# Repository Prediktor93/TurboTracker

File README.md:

# TurboTracker
Line follower robot

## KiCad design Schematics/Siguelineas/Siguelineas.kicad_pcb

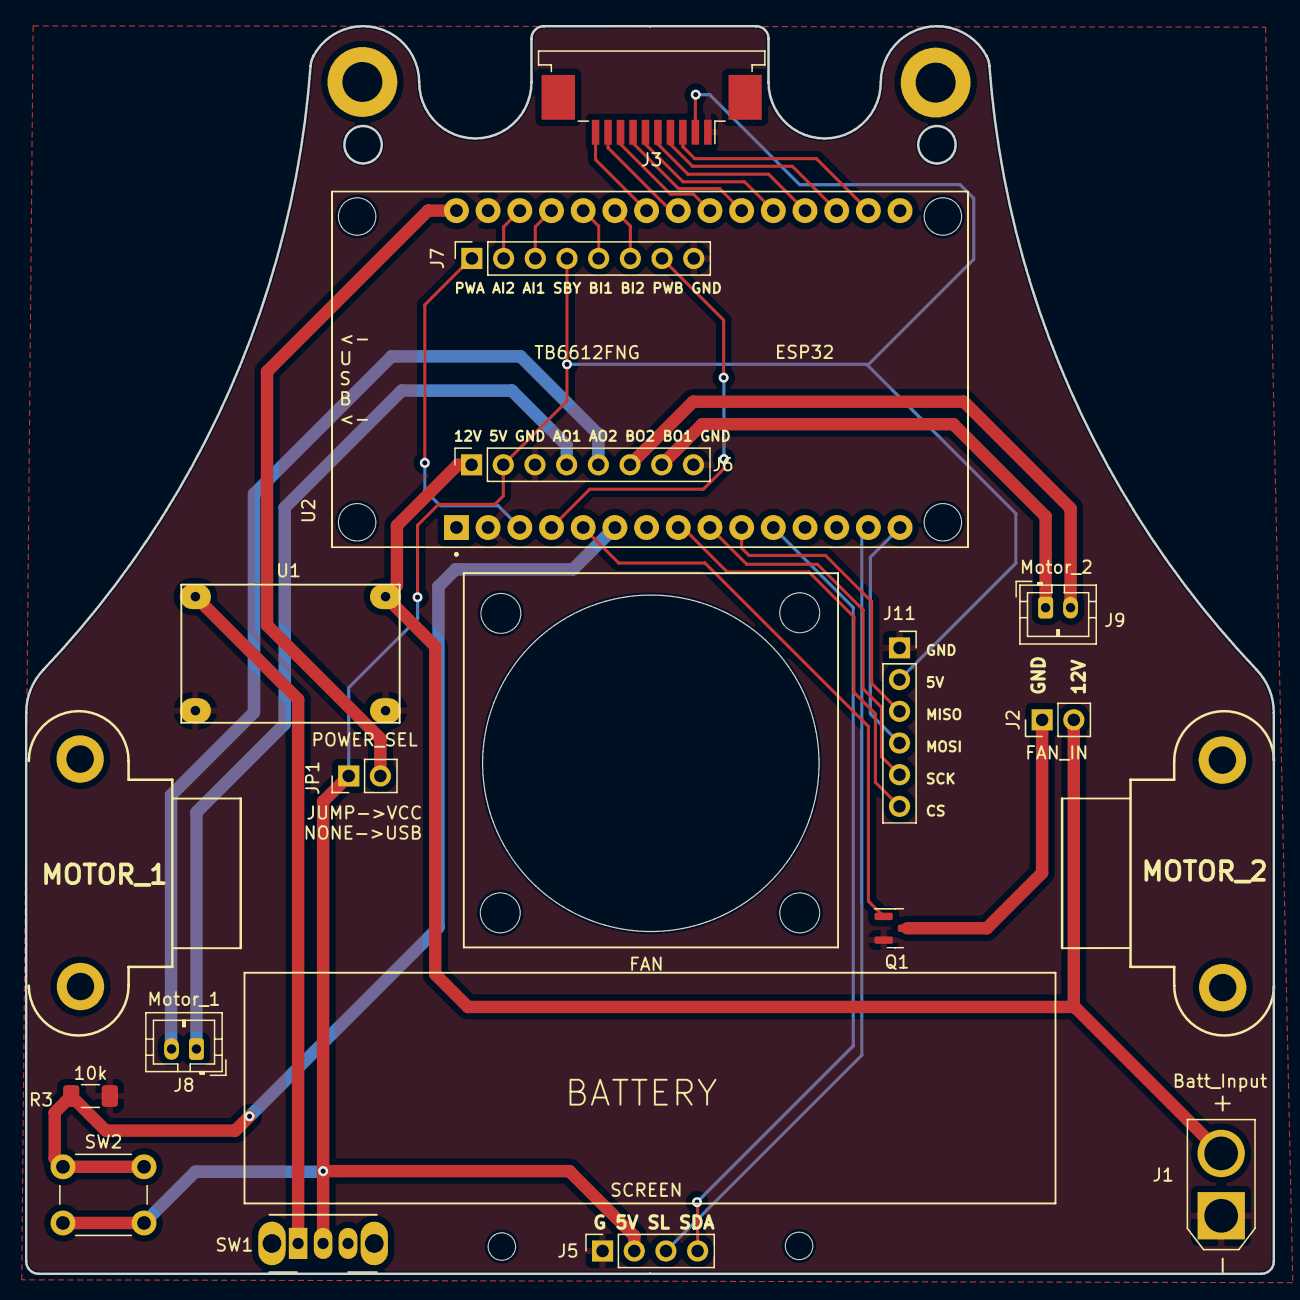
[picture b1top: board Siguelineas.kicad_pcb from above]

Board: 2 copper layers, 100.0 x 100.0 mm, 16 parts (0 on the bottom side), 32 nets.

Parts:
J1: Batt_Input; AMASS_XT30U-M_1x02_P5.0mm_Vertical
J2: FAN_IN; PinHeader_1x02_P2.54mm_Vertical
J3: Line_Sensors; TE_1-84952-0_1x10-1MP_P1.0mm_Horizontal
J5: SCREEN; PinSocket_1x04_P2.54mm_Vertical
J6: TB6612FNG_A; PinSocket_1x08_P2.54mm_Vertical
J7: TB6612FNG_B; PinSocket_1x08_P2.54mm_Vertical
J8: Motor_1; JST_PH_B2B-PH-K_1x02_P2.00mm_Vertical
J9: Motor_2; JST_PH_B2B-PH-K_1x02_P2.00mm_Vertical
J11: SD_con; PinSocket_1x06_P2.54mm_Vertical
JP1: POWER_SEL; PinHeader_1x02_P2.54mm_Vertical
Q1: IRLML2502; SOT-23
R3: 10k; R_1206_3216Metric_Pad1.30x1.75mm_HandSolder
SW1: Switch; SW_CuK_OS102011MA1QN1_SPDT_Angled
SW2: Button 1; SW_PUSH_6mm
U1: Mini360; Mini360_step-down
U2: ESP32-DEVKIT-V1; MODULE_ESP32_DEVKIT_V1

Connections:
+5V: J3.2, J5.2, J6.2, J7.4, J11.2, JP1.1 (A), SW1.2 (B), SW2.2 (D)
+12V: J1.2, J2.2, J6.1, U1.2 (IN+)
BUTTON_1: R3.2, SW2.1 (C), U2.6 (RX2)
FAN: Q1.1 (G), U2.5 (D4)
GND: J1.1, J3.1, J5.1, J6.3, J6.8, J7.8, J11.1, Q1.2 (S), R3.1, U1.1 (IN-), U1.3 (OUT-), U2.2 (GND), U2.29 (GND)
I2C_SCL: J5.3, U2.14 (D22)
I2C_SDA: J5.4, U2.11 (D21)
MOTOR_1_DIR_1: J7.3, U2.27 (D12)
MOTOR_1_DIR_2: J7.2, U2.28 (D13)
MOTOR_1_PWM: J7.1, U2.3 (D15)
MOTOR_2_DIR_1: J7.5, U2.26 (D14)
MOTOR_2_DIR_2: J7.6, U2.25 (D27)
MOTOR_2_PWM: J7.7, U2.4 (D2)
unnamed: J2.1, Q1.3 (D)
unnamed: J6.4, J8.1
unnamed: J6.5, J8.2
unnamed: J6.6, J9.2
unnamed: J6.7, J9.1
unnamed: JP1.2 (B), U2.30 (VIN)
unnamed: SW1.1 (A), U1.4 (OUT+)
SENSOR_1: J3.3, U2.17 (VP)
SENSOR_2: J3.4, U2.18 (VN)
SENSOR_3: J3.5, U2.19 (D34)
SENSOR_4: J3.6, U2.20 (D35)
SENSOR_5: J3.7, U2.21 (D32)
SENSOR_6: J3.8, U2.22 (D33)
SENSOR_7: J3.9, U2.23 (D25)
SENSOR_8: J3.10, U2.24 (D26)
SPI_CS: J11.6, U2.8 (D5)
SPI_MISO: J11.3, U2.10 (D19)
SPI_MOSI: J11.4, U2.15 (D23)
SPI_SCK: J11.5, U2.9 (D18)

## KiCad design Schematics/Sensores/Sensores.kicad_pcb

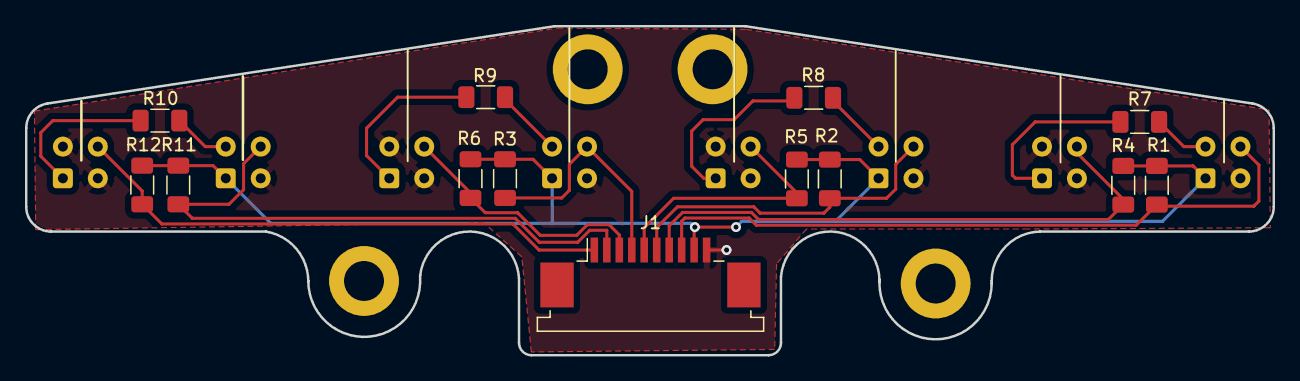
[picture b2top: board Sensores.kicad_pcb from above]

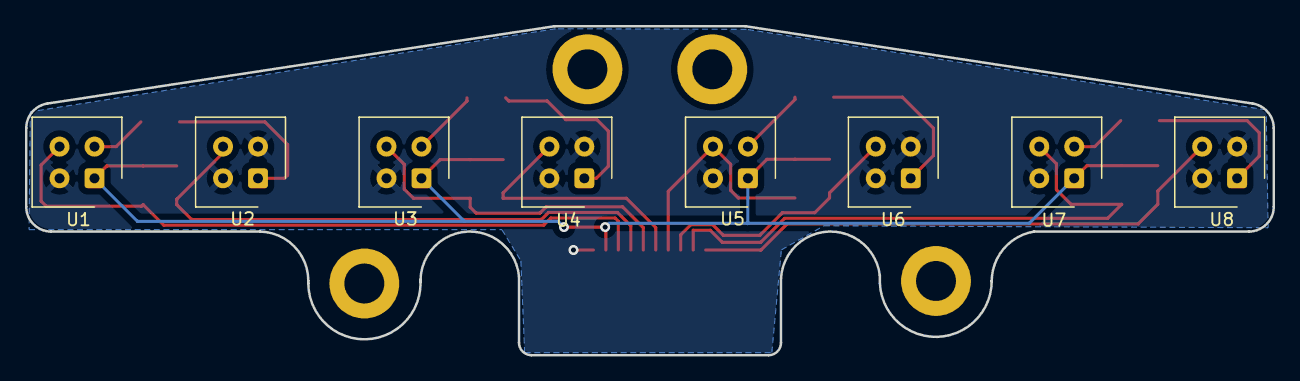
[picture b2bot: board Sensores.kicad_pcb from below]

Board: 2 copper layers, 100.0 x 26.4 mm, 21 parts (8 on the bottom side), 18 nets.

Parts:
J1: Line_sensors; TE_1-84952-0_1x10-1MP_P1.0mm_Horizontal
R1, R2, R3, R4, R5, R6, R11, R12: 10k; R_1206_3216Metric_Pad1.30x1.75mm_HandSolder
R7, R8, R9, R10: 82; R_1206_3216Metric_Pad1.30x1.75mm_HandSolder
U1, U2, U3, U4, U5, U6, U7, U8: CNY70; Vishay_CNY70

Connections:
+5V: J1.9, R1.1, R2.1, R3.1, R4.1, R5.1, R6.1, R11.1, R12.1, U1.1 (A), U3.1 (A), U5.1 (A), U7.1 (A)
GND: J1.10, U1.4 (E), U2.2 (K), U2.4 (E), U3.4 (E), U4.2 (K), U4.4 (E), U5.4 (E), U6.2 (K), U6.4 (E), U7.4 (E), U8.2 (K), U8.4 (E)
unnamed: R7.1, U1.2 (K)
unnamed: R7.2, U2.1 (A)
unnamed: R8.1, U3.2 (K)
unnamed: R8.2, U4.1 (A)
unnamed: R9.1, U5.2 (K)
unnamed: R9.2, U6.1 (A)
unnamed: R10.1, U7.2 (K)
unnamed: R10.2, U8.1 (A)
SENSOR_1: J1.8, R1.2, U1.3 (C)
SENSOR_2: J1.7, R4.2, U2.3 (C)
SENSOR_3: J1.6, R2.2, U3.3 (C)
SENSOR_4: J1.5, R5.2, U4.3 (C)
SENSOR_5: J1.4, R3.2, U5.3 (C)
SENSOR_6: J1.3, R6.2, U6.3 (C)
SENSOR_7: J1.2, R11.2, U7.3 (C)
SENSOR_8: J1.1, R12.2, U8.3 (C)

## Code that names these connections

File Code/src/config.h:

//I2C
#define I2C_MASTER_FREQ_HZ 400000
#define SDA_PIN  GPIO_NUM_21
#define SCL_PIN  GPIO_NUM_22

//SDcard
#define MISO_PIN GPIO_NUM_19
#define MOSI_PIN GPIO_NUM_23
#define SCK_PIN  GPIO_NUM_18
#define CS_PIN   GPIO_NUM_5

//Button
#define BUTTON_1_PIN GPIO_NUM_16

//Motors
#define MOTOR_MAX_SPEED       100
#define MOTOR_1_PWM   GPIO_NUM_15
#define MOTOR_1_DIR_1 GPIO_NUM_12
#define MOTOR_1_DIR_2 GPIO_NUM_13
#define MOTOR_2_PWM   GPIO_NUM_2
#define MOTOR_2_DIR_1 GPIO_NUM_14
#define MOTOR_2_DIR_2 GPIO_NUM_27

//Fan
#define FAN_PIN     GPIO_NUM_4

//Sensors
#define NUM_SENSORS         8
#define SENSOR_1            GPIO_NUM_36
#define SENSOR_2            GPIO_NUM_39
#define SENSOR_3            GPIO_NUM_34
#define SENSOR_4            GPIO_NUM_35
#define SENSOR_5            GPIO_NUM_32
#define SENSOR_6            GPIO_NUM_33
#define SENSOR_7            GPIO_NUM_25
#define SENSOR_8            GPIO_NUM_26

#define SENSOR_1_CHANNEL    ADC1_CHANNEL_0
#define SENSOR_2_CHANNEL    ADC1_CHANNEL_3
#define SENSOR_3_CHANNEL    ADC1_CHANNEL_6
#define SENSOR_4_CHANNEL    ADC1_CHANNEL_7
#define SENSOR_5_CHANNEL    ADC1_CHANNEL_4
#define SENSOR_6_CHANNEL    ADC1_CHANNEL_5
#define SENSOR_7_CHANNEL    ADC2_CHANNEL_8
#define SENSOR_8_CHANNEL    ADC2_CHANNEL_9

//Menu
#define DEFAULT_SPEED_MENU_TIME 15
#define DEFAULT_DIR_MENU_TIME   25

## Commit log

2023-07-19 First code version
2023-07-19 First schematics version
2023-07-19 Added external libraries for schematics
2023-07-19 Components repositioning
2023-07-19 Imu accel calibrated and configured, printed on screen
2023-07-20 SD card working and button interrupt draft
2023-07-20 Minor schematics fixes
2023-07-31 Minor changesç
2023-08-03 Changed motor conectors position
2023-08-04 Version 1.0
2023-08-10 Big clean to remove unused componentes, board reworked, v1.1
2023-09-25 Final Schematics version
2023-09-25 PID working but not tuned
2023-09-25 PID adjust 1
2023-09-27 PID improved
2023-09-28 Before sensor calibration
2023-10-02 Minor adjustments
2023-10-03 Intento watchdog
2023-10-04 Disabled task wdt
2023-10-04 Mutex added and task delay not solved
2023-10-04 Added direction menu
2023-10-06 Final version
